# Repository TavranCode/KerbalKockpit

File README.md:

# KerbalKockpit
A custom control panel for Kerbal Space Program. Heavily cribbed from PeteWasEre

This repository is a place for me to keep and share my code, designs and data for my custom KSP Control Panel.

The contents are:

1. Arduino Code - The modules that run on the Arduino Duemilanove
2. Documentation - Doesn't exist yet!
3. Enclosure Design - The printed graphics used on the panels. Designed to print to a Glowforge
4. PCB design - what it says on the tin.
5. Python Code - The python module that runs at the PC end of the link

If it helps you then please use it. Better yet, consult the original.

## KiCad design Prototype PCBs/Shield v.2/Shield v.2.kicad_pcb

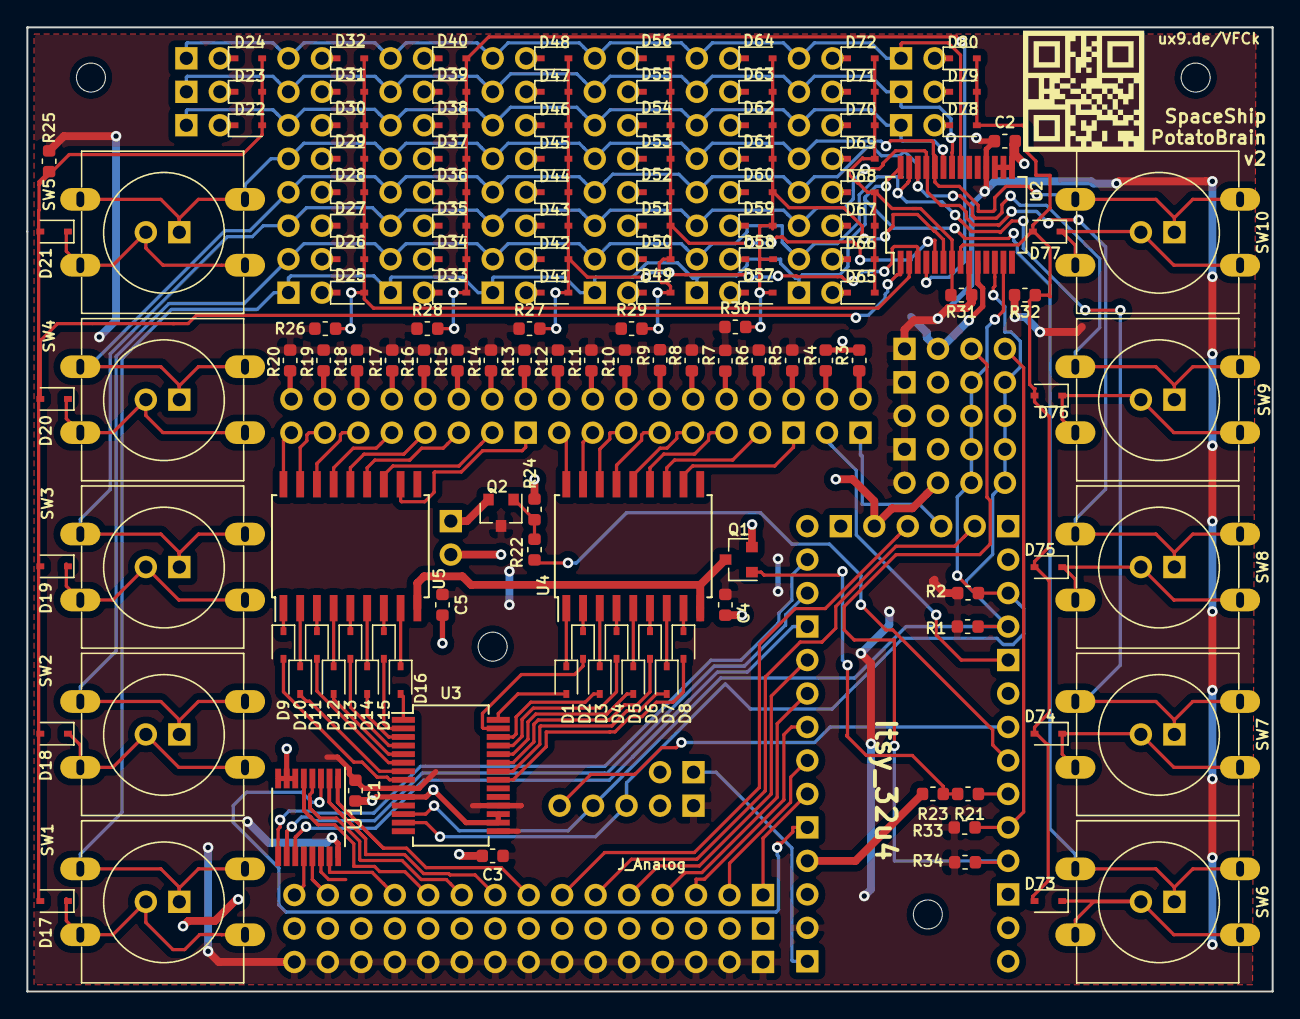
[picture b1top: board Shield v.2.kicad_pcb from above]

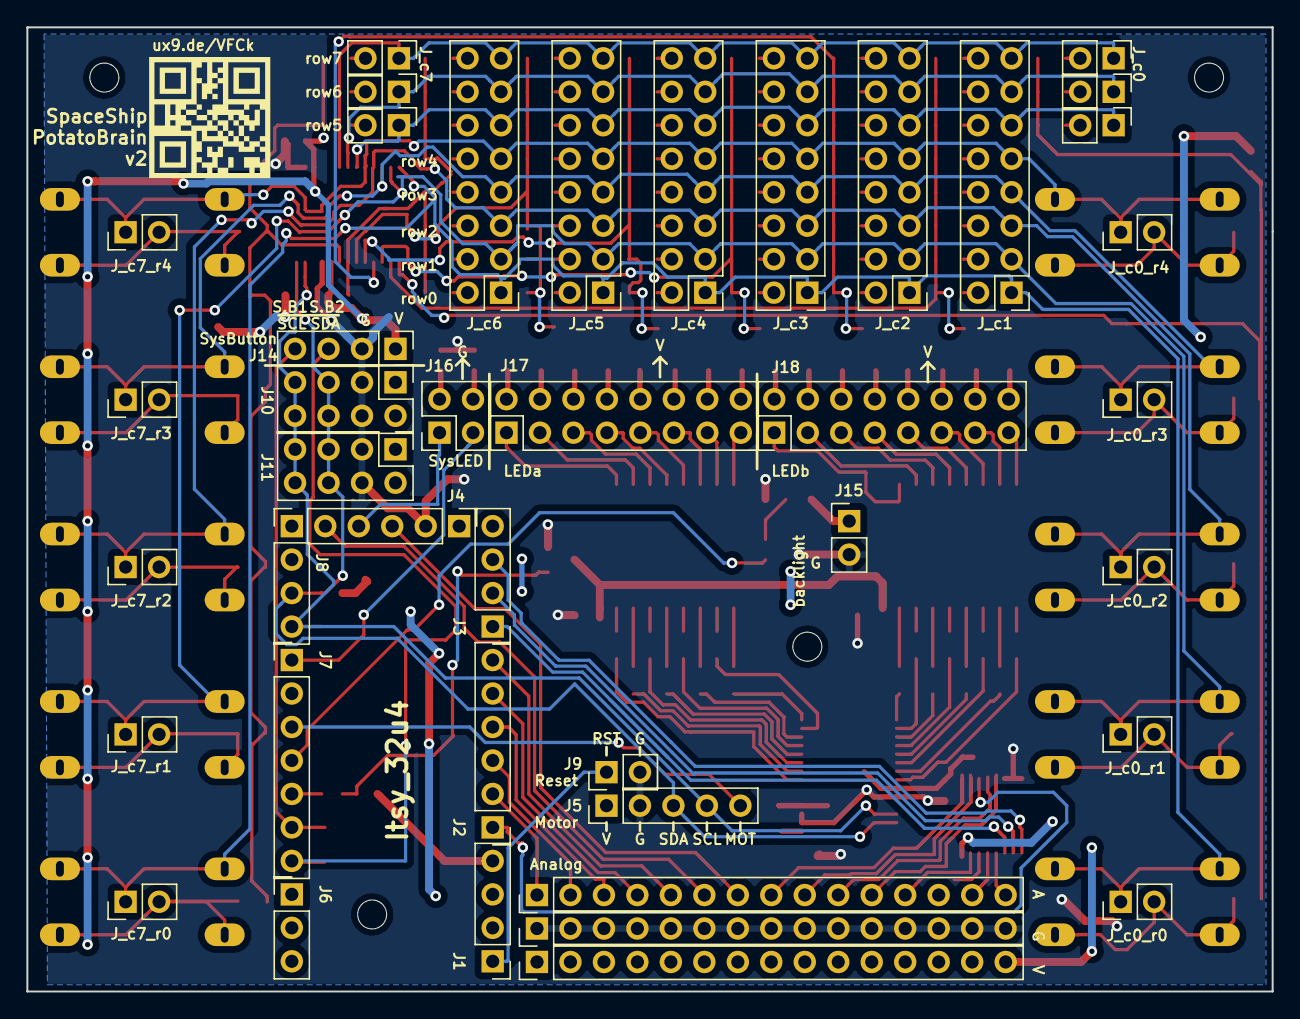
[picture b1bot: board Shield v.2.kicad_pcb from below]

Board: 2 copper layers, 94.5 x 73.2 mm, 183 parts (42 on the bottom side), 181 nets.

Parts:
A: Conn_01x15; PinHeader_1x15_P2.54mm_Vertical
C1, C2, C3, C4, C5: C; C_0603_1608Metric
D1, D2, D3, D4, D5, D6, D7, D8, D9, D10, D11, D12, D13, D14, D15, D16: D; D_SOD-323
D17, D18, D19, D20, D21, D22, D23, D24, D25, D26, D27, D28, D29, D30, D31, D32, D33, D34, D35, D36, D37, D38, D39, D40, D41, D42, D43, D44, D45, D46, D47, D48, D49, D50, D51, D52, D53, D54, D55, D56, D57, D58, D59, D60, D61, D62, D63, D64, D65, D66, D67, D68, D69, D70, D71, D72, D73, D74, D75, D76, D77, D78, D79, D80: 1N4148; D_SOD-323
G: Conn_01x15; PinHeader_1x15_P2.54mm_Vertical
J1, J3, J8: Conn_01x04; PinHeader_1x04_P2.54mm_Vertical
J2: Conn_01x06; PinHeader_1x06_P2.54mm_Vertical
J4: Conn_01x05; PinHeader_1x05_P2.54mm_Vertical
J5: Motor; PinHeader_1x05_P2.54mm_Vertical
J6: Conn_01x03; PinHeader_1x03_P2.54mm_Vertical
J7: Conn_01x07; PinHeader_1x07_P2.54mm_Vertical
J9: Conn_Reset; PinHeader_1x02_P2.54mm_Vertical
J10: i2cA; PinHeader_2x04_P2.54mm_Vertical
J11: i2cB; PinHeader_2x04_P2.54mm_Vertical
J14: Conn_SysBut; PinHeader_1x04_P2.54mm_Vertical
J15: Conn_bLight; PinHeader_1x02_P2.54mm_Vertical
J16: Conn_SysLED; PinHeader_2x02_P2.54mm_Vertical
J17: LEDs_A; PinHeader_2x08_P2.54mm_Vertical
J18: LEDs_B; PinHeader_2x08_P2.54mm_Vertical
J19F2, J19G1, J26F1, J26G1: Jumper_NO_Small; PinHeader_1x02_P2.54mm_Vertical
J_c0, J_c0_r0, J_c0_r1, J_c0_r2, J_c0_r3, J_c0_r4, J_c7, J_c7_r0, J_c7_r1, J_c7_r2, J_c7_r3, J_c7_r4: Jumper_NO_Small; PinHeader_1x02_P2.54mm_Vertical
J_c1, J_c2, J_c3, J_c4, J_c5, J_c6: JumpSwitch; PinHeader_2x08_P2.54mm_Vertical
Mount1, Mount2, Mount3, Mount4: MountingHole_2.2mm_M2
Q1, Q2: Q_NMOS_DIM; SOT-23
QR*****: ux9.de/VFCk; ux9.de_VFCk
QR*****#2: ux9.de/VFCk; ux9.de_VFCk
R1, R2, R23, R24, R25, R26, R27, R28, R29, R30, R31, R32, R33, R34: R4.7k; R_0603_1608Metric
R3, R4, R5, R6, R7, R8, R9, R10, R11, R12, R13, R14, R15, R16, R17, R18, R19, R20: R; R_0603_1608Metric
R21, R22: R1k; R_0603_1608Metric
SW1, SW2, SW3, SW4, SW5, SW6, SW7, SW8, SW9, SW10: SW_Push; SW_PUSH-12mm_widepinholes
U1: 74HC4051; TSSOP-16_4.4x5mm_P0.65mm
U2: MCP23017_0x20_in; SSOP-28_5.3x10.2mm_P0.65mm
U3: MCP23017_0x21_out; SSOP-28_5.3x10.2mm_P0.65mm
U4, U5: ULN2803A; SOIC-18W_7.5x11.6mm_P1.27mm
V: Conn_01x15; PinHeader_1x15_P2.54mm_Vertical

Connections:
+5V: C1.1, C2.1, C3.1, C4.1, C5.1, J1.2, J5.1, J10.1, J10.2, J11.1, J11.2, J14.1, Q2.3, R1.1, R2.1, R5.1, R6.1, R7.1, R8.1, R9.1, R10.1, R11.1, R12.1, R13.1, R14.1, R15.1, R16.1, R17.1, R18.1, R19.1, R20.1, R25.1, R26.1, R27.1, R28.1, R29.1, R30.1, R31.1, R32.1, R33.1, R34.1, U1.16, U2.9, U2.18, U3.9, U3.15, U3.18, V.1, V.2, V.3, V.4, V.5, V.6, V.7, V.8, V.9, V.10, V.11, V.12, V.13, V.14, V.15
/5*: J7.1, J16.3
/9*: J5.5, J7.3
/10*: J7.4, R22.2
/11*: J7.5, R21.2
/12: J7.6, J14.4, R33.2
/13: J7.7, J14.3, R34.2
/14: J3.3, U1.9
/15: J3.1, U1.11
/16: J3.2, U1.10
/A0: J2.1, U1.3
/A1: A.1, J2.2
/A2: A.2, J2.3
/A3: A.3, J2.4
/A4: A.4, J2.5
/A5: A.5, J2.6
/A6: A.6, J4.5
/A7: J4.4, J16.1
/A8: A.7, J4.3
/DIM: Q1.3, U4.9, U5.9
/Input Matrix/input_c0: D17.2, D18.2, D19.2, D20.2, D21.2, D22.2, D23.2, D24.2, R25.2, U2.1
/Input Matrix/input_c1: D25.2, D26.2, D27.2, D28.2, D29.2, D30.2, D31.2, D32.2, R26.2, U2.2
/Input Matrix/input_c2: D33.2, D34.2, D35.2, D36.2, D37.2, D38.2, D39.2, D40.2, R28.2, U2.4
/Input Matrix/input_c3: D41.2, D42.2, D43.2, D44.2, D45.2, D46.2, D47.2, D48.2, R27.2, U2.3
/Input Matrix/input_c4: D49.2, D50.2, D51.2, D52.2, D53.2, D54.2, D55.2, D56.2, R29.2, U2.5
/Input Matrix/input_c5: D57.2, D58.2, D59.2, D60.2, D61.2, D62.2, D63.2, D64.2, R30.2, U2.6
/Input Matrix/input_c6: D65.2, D66.2, D67.2, D68.2, D69.2, D70.2, D71.2, D72.2, R31.2, U2.7
/Input Matrix/input_c7: D73.2, D74.2, D75.2, D76.2, D77.2, D78.2, D79.2, D80.2, R32.2, U2.8
/Input Matrix/input_r0: J_c0_r0.1, J_c1.1, J_c2.1, J_c3.1, J_c4.1, J_c5.1, J_c6.1, J_c7_r0.1, SW1.1, SW6.1, U2.28
/Input Matrix/input_r1: J_c0_r1.1, J_c1.3, J_c2.3, J_c3.3, J_c4.3, J_c5.3, J_c6.3, J_c7_r1.1, SW2.1, SW7.1, U2.27
/Input Matrix/input_r2: J_c0_r2.1, J_c1.5, J_c2.5, J_c3.5, J_c4.5, J_c5.5, J_c6.5, J_c7_r2.1, SW3.1, SW8.1, U2.25
/Input Matrix/input_r3: J_c0_r3.1, J_c1.7, J_c2.7, J_c3.7, J_c4.7, J_c5.7, J_c6.7, J_c7_r3.1, SW4.1, SW9.1, U2.26
/Input Matrix/input_r4: J_c0_r4.1, J_c1.9, J_c2.9, J_c3.9, J_c4.9, J_c5.9, J_c6.9, J_c7_r4.1, SW5.1, SW10.1, U2.24
/Input Matrix/input_r5: J19F2.1, J26F1.1, J_c1.11, J_c2.11, J_c3.11, J_c4.11, J_c5.11, J_c6.11, U2.23
/Input Matrix/input_r6: J19G1.1, J26G1.1, J_c1.13, J_c2.13, J_c3.13, J_c4.13, J_c5.13, J_c6.13, U2.22
/Input Matrix/input_r7: J_c0.1, J_c1.15, J_c2.15, J_c3.15, J_c4.15, J_c5.15, J_c6.15, J_c7.1, U2.21
/O.A0: D9.1, U5.1
/O.A1: D10.1, U5.2
/O.A2: D11.1, U5.3
/O.A3: D12.1, U5.4
/O.A4: D13.1, U5.5
/O.A5: D14.1, U5.6
/O.A6: D15.1, U5.7
/O.A7: D16.1, U5.8
/O.B0: D1.1, U4.1
/O.B1: D2.1, U4.2
/O.B2: D3.1, U4.3
/O.B3: D4.1, U4.4
/O.B4: D5.1, U4.5
/O.B5: D6.1, U4.6
/O.B6: D7.1, U4.7
/O.B7: D8.1, U4.8
/RST: J1.1, J9.1
/SCL: J5.4, J8.4, J10.7, J10.8, J11.7, J11.8, R1.2, U2.12, U3.12
/SDA: J5.3, J8.3, J10.5, J10.6, J11.5, J11.6, R2.2, U2.13, U3.13
/uA0: A.14, U1.13
/uA1: A.13, U1.14
/uA2: A.12, U1.15
/uA3: A.15, U1.12
/uA4: A.8, U1.1
/uA5: A.11, U1.5
/uA6: A.9, U1.2
/uA7: A.10, U1.4
GND: C1.2, C2.2, C3.2, C4.2, C5.2, G.1, G.2, G.3, G.4, G.5, G.6, G.7, G.8, G.9, G.10, G.11, G.12, G.13, G.14, G.15, J1.4, J4.2, J5.2, J9.2, J10.3, J10.4, J11.3, J11.4, J14.2, J15.2, Q1.2, R3.1, R4.1, R23.1, R24.1, U1.6, U1.7, U1.8, U2.10, U2.15, U2.16, U2.17, U3.10, U3.16, U3.17
unnamed: D1.2, U3.28
unnamed: D2.2, U3.27
unnamed: D3.2, U3.26
unnamed: D4.2, U3.25
unnamed: D5.2, U3.24
unnamed: D6.2, U3.23
unnamed: D7.2, U3.22
unnamed: D8.2, U3.21
unnamed: D9.2, U3.8
unnamed: D10.2, U3.7
unnamed: D11.2, U3.6
unnamed: D12.2, U3.5
unnamed: D13.2, U3.4
unnamed: D14.2, U3.3
unnamed: D15.2, U3.2
unnamed: D16.2, U3.1
unnamed: D17.1, J_c0_r0.2, SW1.2
unnamed: D18.1, J_c0_r1.2, SW2.2
unnamed: D19.1, J_c0_r2.2, SW3.2
unnamed: D20.1, J_c0_r3.2, SW4.2
unnamed: D21.1, J_c0_r4.2, SW5.2
unnamed: D22.1, J19F2.2
unnamed: D23.1, J19G1.2
unnamed: D24.1, J_c0.2
unnamed: D25.1, J_c1.2
unnamed: D26.1, J_c1.4
unnamed: D27.1, J_c1.6
unnamed: D28.1, J_c1.8
unnamed: D29.1, J_c1.10
unnamed: D30.1, J_c1.12
unnamed: D31.1, J_c1.14
unnamed: D32.1, J_c1.16
unnamed: D33.1, J_c2.2
unnamed: D34.1, J_c2.4
unnamed: D35.1, J_c2.6
unnamed: D36.1, J_c2.8
unnamed: D37.1, J_c2.10
unnamed: D38.1, J_c2.12
unnamed: D39.1, J_c2.14
unnamed: D40.1, J_c2.16
unnamed: D41.1, J_c3.2
unnamed: D42.1, J_c3.4
unnamed: D43.1, J_c3.6
unnamed: D44.1, J_c3.8
unnamed: D45.1, J_c3.10
unnamed: D46.1, J_c3.12
unnamed: D47.1, J_c3.14
unnamed: D48.1, J_c3.16
unnamed: D49.1, J_c4.2
unnamed: D50.1, J_c4.4
unnamed: D51.1, J_c4.6
unnamed: D52.1, J_c4.8
unnamed: D53.1, J_c4.10
unnamed: D54.1, J_c4.12
unnamed: D55.1, J_c4.14
unnamed: D56.1, J_c4.16
unnamed: D57.1, J_c5.2
unnamed: D58.1, J_c5.4
unnamed: D59.1, J_c5.6
unnamed: D60.1, J_c5.8
unnamed: D61.1, J_c5.10
unnamed: D62.1, J_c5.12
unnamed: D63.1, J_c5.14
unnamed: D64.1, J_c5.16
unnamed: D65.1, J_c6.2
unnamed: D66.1, J_c6.4
unnamed: D67.1, J_c6.6
unnamed: D68.1, J_c6.8
unnamed: D69.1, J_c6.10
unnamed: D70.1, J_c6.12
unnamed: D71.1, J_c6.14
unnamed: D72.1, J_c6.16
unnamed: D73.1, J_c7_r0.2, SW6.2
unnamed: D74.1, J_c7_r1.2, SW7.2
unnamed: D75.1, J_c7_r2.2, SW8.2
unnamed: D76.1, J_c7_r3.2, SW9.2
unnamed: D77.1, J_c7_r4.2, SW10.2
unnamed: D78.1, J26F1.2
unnamed: D79.1, J26G1.2
unnamed: D80.1, J_c7.2
unnamed: J15.1, Q2.2
unnamed: J16.2, R3.2
unnamed: J16.4, R4.2
unnamed: J17.1, U4.11
unnamed: J17.2, R5.2
unnamed: J17.3, U4.12
unnamed: J17.4, R6.2
unnamed: J17.5, U4.13
unnamed: J17.6, R7.2
unnamed: J17.7, U4.14
unnamed: J17.8, R8.2
unnamed: J17.9, U4.15
unnamed: J17.10, R9.2
unnamed: J17.11, U4.16
unnamed: J17.12, R10.2
unnamed: J17.13, U4.17
unnamed: J17.14, R11.2
unnamed: J17.15, U4.18
unnamed: J17.16, R12.2
unnamed: J18.1, U5.11
unnamed: J18.2, R13.2
unnamed: J18.3, U5.12
unnamed: J18.4, R14.2
unnamed: J18.5, U5.13
unnamed: J18.6, R15.2
unnamed: J18.7, U5.14
unnamed: J18.8, R16.2
unnamed: J18.9, U5.15
unnamed: J18.10, R17.2
unnamed: J18.11, U5.16
unnamed: J18.12, R18.2
unnamed: J18.13, U5.17
unnamed: J18.14, R19.2
unnamed: J18.15, U5.18
unnamed: J18.16, R20.2
unnamed: Q1.1, R21.1, R23.2
unnamed: Q2.1, R22.1, R24.2

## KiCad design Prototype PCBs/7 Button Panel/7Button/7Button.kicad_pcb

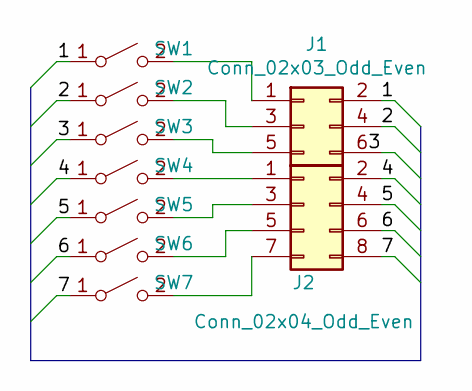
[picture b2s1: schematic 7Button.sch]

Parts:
J1: Conn_02x03_Odd_Even; PinHeader_2x03_P2.54mm_Vertical
J2: Conn_02x04_Odd_Even; PinHeader_2x04_P2.54mm_Vertical
SW1, SW2, SW3, SW4, SW5, SW6, SW7: SW_SPST; SW_PUSH-12mm_widepinholes

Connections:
/1: J1.2, SW1.1 (A)
/2: J1.4, SW2.1 (A)
/3: J1.6, SW3.1 (A)
/4: J2.2, SW4.1 (A)
/5: J2.4, SW5.1 (A)
/6: J2.6, SW6.1 (A)
/7: J2.8, SW7.1 (A)
unnamed: J1.1, SW1.2 (B)
unnamed: J1.3, SW2.2 (B)
unnamed: J1.5, SW3.2 (B)
unnamed: J2.1, SW4.2 (B)
unnamed: J2.3, SW5.2 (B)
unnamed: J2.5, SW6.2 (B)
unnamed: J2.7, SW7.2 (B)

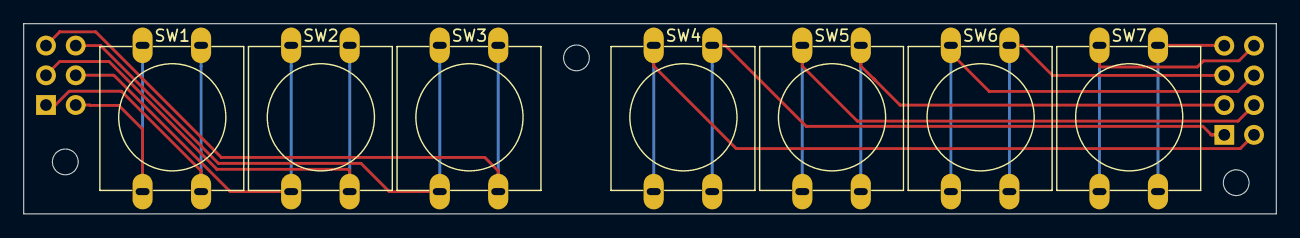
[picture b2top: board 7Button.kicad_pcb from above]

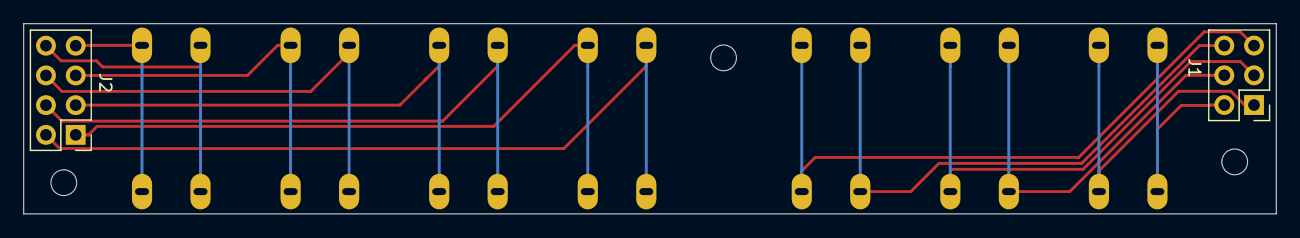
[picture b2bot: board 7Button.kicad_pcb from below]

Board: 2 copper layers, 107.1 x 16.3 mm, 9 parts (2 on the bottom side), 14 nets.

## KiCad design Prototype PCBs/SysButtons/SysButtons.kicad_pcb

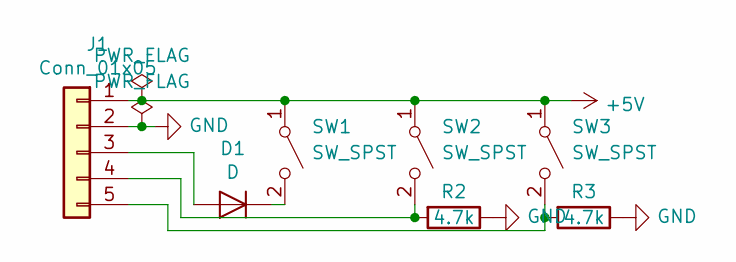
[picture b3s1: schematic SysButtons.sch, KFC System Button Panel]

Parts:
D1: D; D_DO-35_SOD27_P7.62mm_Horizontal
J1: Conn_01x05; PinHeader_1x05_P2.54mm_Vertical
R2, R3: 4.7k; R_Axial_DIN0207_L6.3mm_D2.5mm_P7.62mm_Horizontal
SW1, SW2, SW3: SW_SPST; SW_PUSH-12mm_widepinholes

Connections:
+5V: J1.1, SW1.1 (A), SW2.1 (A), SW3.1 (A)
GND: J1.2, R2.1, R3.1
unnamed: D1.1 (K), SW1.2 (B)
unnamed: D1.2 (A), J1.3
unnamed: J1.4, R2.2, SW2.2 (B)
unnamed: J1.5, R3.2, SW3.2 (B)

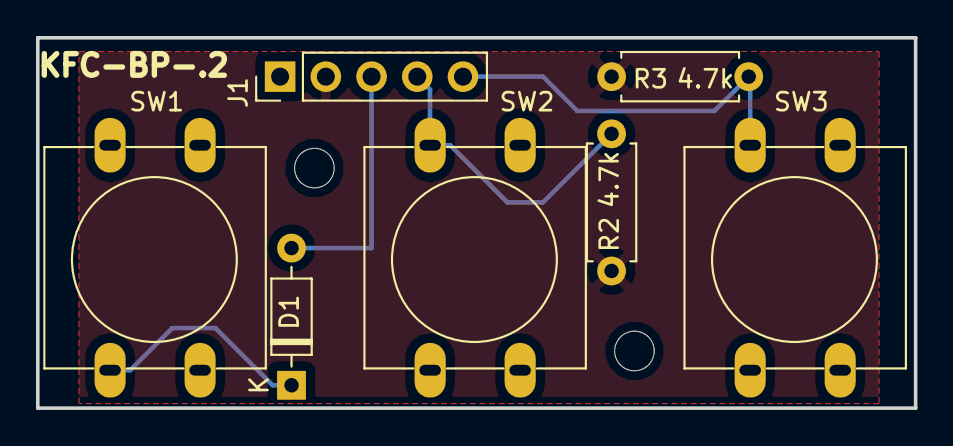
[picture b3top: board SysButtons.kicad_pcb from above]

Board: 2 copper layers, 48.8 x 20.6 mm, 7 parts (0 on the bottom side), 6 nets.

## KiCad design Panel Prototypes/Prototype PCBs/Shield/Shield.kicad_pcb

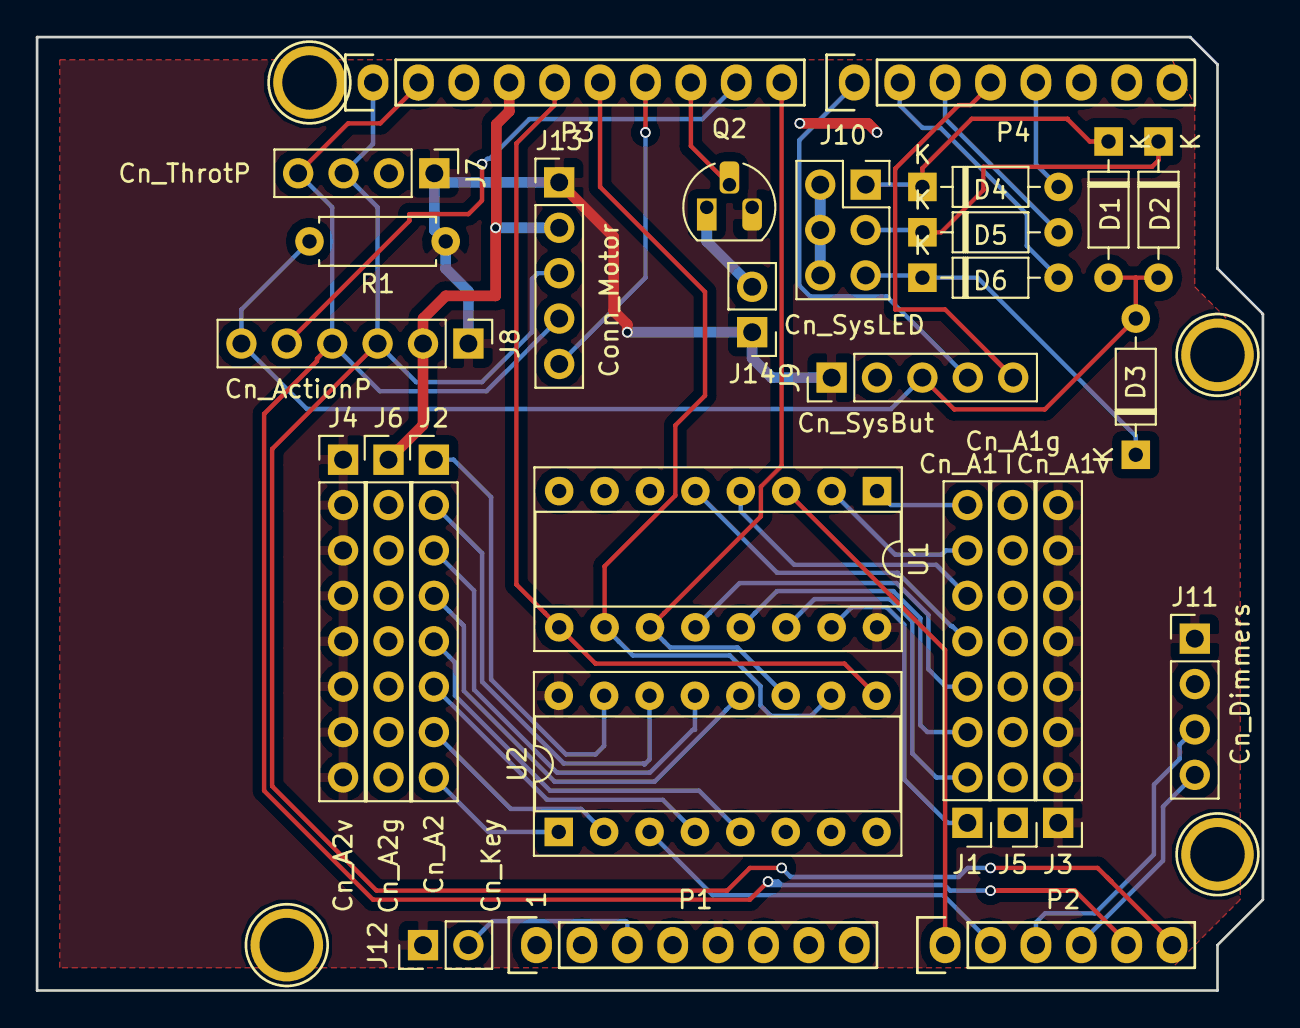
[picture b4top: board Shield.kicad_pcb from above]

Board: 2 copper layers, 68.6 x 53.3 mm, 32 parts (0 on the bottom side), 41 nets.

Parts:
D1, D2, D3, D4, D5, D6: D; D_DO-35_SOD27_P7.62mm_Horizontal
J1: Cn_A1; PinHeader_1x08_P2.54mm_Vertical
J2: Cn_A2; PinHeader_1x08_P2.54mm_Vertical
J3: Cn_A1v; PinHeader_1x08_P2.54mm_Vertical
J4: Cn_A2v; PinHeader_1x08_P2.54mm_Vertical
J5: Cn_A1g; PinHeader_1x08_P2.54mm_Vertical
J6: Cn_A2g; PinHeader_1x08_P2.54mm_Vertical
J7: Cn_ThrotP; PinHeader_1x04_P2.54mm_Vertical
J8: Cn_ActionP; PinHeader_1x06_P2.54mm_Vertical
J9: Cn_SysBut; PinHeader_1x05_P2.54mm_Vertical
J10: Cn_SysLED; PinSocket_2x03_P2.54mm_Vertical
J11: Cn_Dimmers; PinHeader_1x04_P2.54mm_Vertical
J12: Cn_Key; PinHeader_1x02_P2.54mm_Vertical
J13: Conn_Motor; PinHeader_1x05_P2.54mm_Vertical
J14: Cn_Back; PinHeader_1x02_P2.54mm_Vertical
P1: Power; Socket_Strip_Arduino_1x08
P2: Analog; Socket_Strip_Arduino_1x06
P3: Digital; Socket_Strip_Arduino_1x10
P4: Digital; Socket_Strip_Arduino_1x08
P5, P6, P7, P8: CONN_01X01; Arduino_1pin
Q2: 2N2219; TO-92_HandSolder
R1: 10k; R_Axial_DIN0207_L6.3mm_D2.5mm_P7.62mm_Horizontal
U1, U2: 74HC4051; DIP-16_W7.62mm_Socket

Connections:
+5V: J3.1, J3.2, J3.3, J3.4, J3.5, J3.6, J3.7, J3.8, J4.1, J4.2, J4.3, J4.4, J4.5, J4.6, J4.7, J4.8, J7.1, J8.1, J9.1, J11.1, J12.1, J13.1, J14.1, P1.5, Q2.3, R1.1, U1.16, U2.16
/3(**): D4.2, P4.5
/4: J9.5, P4.4
/5(**): D5.2, P4.3
/6(**): D6.2, P4.2
/7: J9.4, P4.1
/8: P3.10, U1.11, U2.11
/9(**): J8.5, P3.9
/10(**/SS): P3.8, Q2.2
/11(**/MOSI): J13.5, P3.7
/12(MISO): P3.6, U1.10, U2.10
/13(SCK): P3.5, U1.9, U2.9
/A0: P2.1, U1.3
/A1: P2.2, U2.3
/A2: J11.3, P2.3
/A3: J11.4, P2.4
/A4(SDA): J7.4, J8.4, J13.4, P2.5, P3.2
/A5(SCL): J7.3, J8.3, J13.3, P2.6, P3.1
/Au1: J2.4, U2.12
/Au2: J2.8, U2.1
/Au3: J2.5, U2.5
/Au4: J2.7, U2.2
/Au5: J2.6, U2.4
/Crx: J1.8, U1.1
/Cry: J1.5, U1.5
/Ctx: J1.7, U1.2
/Cty: J1.6, U1.4
/Ltest: D1.2, D2.2, D3.2, J8.6, J9.3, R1.2
/R_x: J2.3, U2.13
/R_y: J2.2, U2.14
/R_z: J2.1, U2.15
/Reset: J12.2, P1.3
/T_x: J1.3, U1.13
/T_y: J1.2, U1.14
/T_z: J1.1, U1.15
/Thr: J1.4, U1.12
GND: J5.1, J5.2, J5.3, J5.4, J5.5, J5.6, J5.7, J5.8, J6.1, J6.2, J6.3, J6.4, J6.5, J6.6, J6.7, J6.8, J7.2, J8.2, J9.2, J10.2, J10.4, J10.6, J11.2, J13.2, P1.6, P1.7, P3.4, U1.6, U1.7, U1.8, U2.6, U2.7, U2.8
unnamed: D1.1, D4.1, J10.1
unnamed: D2.1, D5.1, J10.3
unnamed: D3.1, D6.1, J10.5
unnamed: J14.2, Q2.1

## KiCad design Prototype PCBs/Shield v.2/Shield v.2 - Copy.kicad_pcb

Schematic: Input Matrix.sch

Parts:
D1, D2, D3, D4, D5, D6, D7, D8, D9, D10, D11, D12, D13, D14, D15, D16, D17, D18, D19, D20, D21, D22, D23, D24, D25, D26, D27, D28, D29, D30, D31, D32, D33, D34, D35, D36, D37, D38, D39, D40, D41, D42, D43, D44, D45, D46, D47, D48, D49, D50, D51, D52, D53, D54, D55, D56, D57, D58, D59, D60, D61, D62, D63, D64: 1N4148; D_SOD-323
J1, J2, J3, J4, J5, J6, J7, J8: JumpSwitch; PinHeader_2x08_P2.54mm_Vertical
SW1, SW2, SW3, SW4, SW5, SW6, SW7, SW8, SW9, SW10: SW_Push; SW_SPST_B3S-1000

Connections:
/Input Matrix/input_c0: D1.2 (A), D2.2 (A), D6.2 (A), D7.2 (A), D8.2 (A); also elsewhere on the board
/Input Matrix/input_c1: D9.2 (A), D10.2 (A), D11.2 (A), D12.2 (A), D13.2 (A), D14.2 (A), D15.2 (A), D16.2 (A); also elsewhere on the board
/Input Matrix/input_c2: D17.2 (A), D18.2 (A), D19.2 (A), D20.2 (A), D21.2 (A), D22.2 (A), D23.2 (A), D24.2 (A); also elsewhere on the board
/Input Matrix/input_c3: D25.2 (A), D26.2 (A), D27.2 (A), D28.2 (A), D29.2 (A), D30.2 (A), D31.2 (A), D32.2 (A); also elsewhere on the board
/Input Matrix/input_c4: D33.2 (A), D34.2 (A), D35.2 (A), D36.2 (A), D37.2 (A), D38.2 (A), D39.2 (A), D40.2 (A); also elsewhere on the board
/Input Matrix/input_c5: D41.2 (A), D42.2 (A), D43.2 (A), D44.2 (A), D45.2 (A), D46.2 (A), D47.2 (A), D48.2 (A); also elsewhere on the board
/Input Matrix/input_c6: D49.2 (A), D50.2 (A), D51.2 (A), D52.2 (A), D53.2 (A), D54.2 (A), D55.2 (A), D56.2 (A); also elsewhere on the board
/Input Matrix/input_c7: D57.2 (A), D58.2 (A), D59.2 (A), D60.2 (A), D61.2 (A), D62.2 (A), D63.2 (A), D64.2 (A); also elsewhere on the board
/Input Matrix/input_r0: J1.1, J2.1, J3.1, J4.1, J5.1, J6.1, J7.1, J8.1, SW1.1, SW6.1; also elsewhere on the board
/Input Matrix/input_r1: J1.3, J2.3, J3.3, J4.3, J5.3, J6.3, J7.3, J8.3, SW2.1, SW7.1; also elsewhere on the board
/Input Matrix/input_r2: J2.5, J3.5, J4.5, J5.5, J6.5, J7.5, J8.5, SW3.1, SW8.1; also elsewhere on the board
/Input Matrix/input_r3: J2.7, J3.7, J4.7, J5.7, J6.7, J7.7, J8.7, SW4.1, SW9.1; also elsewhere on the board
/Input Matrix/input_r4: J2.9, J3.9, J4.9, J5.9, J6.9, J7.9, J8.9, SW5.1, SW10.1; also elsewhere on the board
/Input Matrix/input_r5: J1.11, J2.11, J3.11, J4.11, J5.11, J6.11, J7.11, J8.11; also elsewhere on the board
/Input Matrix/input_r6: J1.13, J2.13, J3.13, J4.13, J5.13, J6.13, J7.13, J8.13; also elsewhere on the board
/Input Matrix/input_r7: J1.15, J2.15, J3.15, J4.15, J5.15, J6.15, J7.15, J8.15; also elsewhere on the board
unnamed: D1.1 (K), J1.2, SW1.2
unnamed: D2.1 (K), J1.4, SW2.2
unnamed: D3.1 (K), J1.6, SW3.2
unnamed: D4.1 (K), J1.8, SW4.2
unnamed: D5.1 (K), J1.10, SW5.2
unnamed: D6.1 (K), J1.12
unnamed: D7.1 (K), J1.14
unnamed: D8.1 (K), J1.16
unnamed: D9.1 (K), J2.2
unnamed: D10.1 (K), J2.4
unnamed: D11.1 (K), J2.6
unnamed: D12.1 (K), J2.8
unnamed: D13.1 (K), J2.10
unnamed: D14.1 (K), J2.12
unnamed: D15.1 (K), J2.14
unnamed: D16.1 (K), J2.16
unnamed: D17.1 (K), J3.2
unnamed: D18.1 (K), J3.4
unnamed: D19.1 (K), J3.6
unnamed: D20.1 (K), J3.8
unnamed: D21.1 (K), J3.10
unnamed: D22.1 (K), J3.12
unnamed: D23.1 (K), J3.14
unnamed: D24.1 (K), J3.16
unnamed: D25.1 (K), J4.2
unnamed: D26.1 (K), J4.4
unnamed: D27.1 (K), J4.6
unnamed: D28.1 (K), J4.8
unnamed: D29.1 (K), J4.10
unnamed: D30.1 (K), J4.12
unnamed: D31.1 (K), J4.14
unnamed: D32.1 (K), J4.16
unnamed: D33.1 (K), J5.2
unnamed: D34.1 (K), J5.4
unnamed: D35.1 (K), J5.6
unnamed: D36.1 (K), J5.8
unnamed: D37.1 (K), J5.10
unnamed: D38.1 (K), J5.12
unnamed: D39.1 (K), J5.14
unnamed: D40.1 (K), J5.16
unnamed: D41.1 (K), J6.2
unnamed: D42.1 (K), J6.4
unnamed: D43.1 (K), J6.6
unnamed: D44.1 (K), J6.8
unnamed: D45.1 (K), J6.10
unnamed: D46.1 (K), J6.12
unnamed: D47.1 (K), J6.14
unnamed: D48.1 (K), J6.16
unnamed: D49.1 (K), J7.2
unnamed: D50.1 (K), J7.4
unnamed: D51.1 (K), J7.6
unnamed: D52.1 (K), J7.8
unnamed: D53.1 (K), J7.10
unnamed: D54.1 (K), J7.12
unnamed: D55.1 (K), J7.14
unnamed: D56.1 (K), J7.16
unnamed: D57.1 (K), J8.2, SW6.2
unnamed: D58.1 (K), J8.4, SW7.2
unnamed: D59.1 (K), J8.6, SW8.2
unnamed: D60.1 (K), J8.8, SW9.2
unnamed: D61.1 (K), J8.10, SW10.2
unnamed: D62.1 (K), J8.12
unnamed: D63.1 (K), J8.14
unnamed: D64.1 (K), J8.16

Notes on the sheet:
Shield V2 8x8

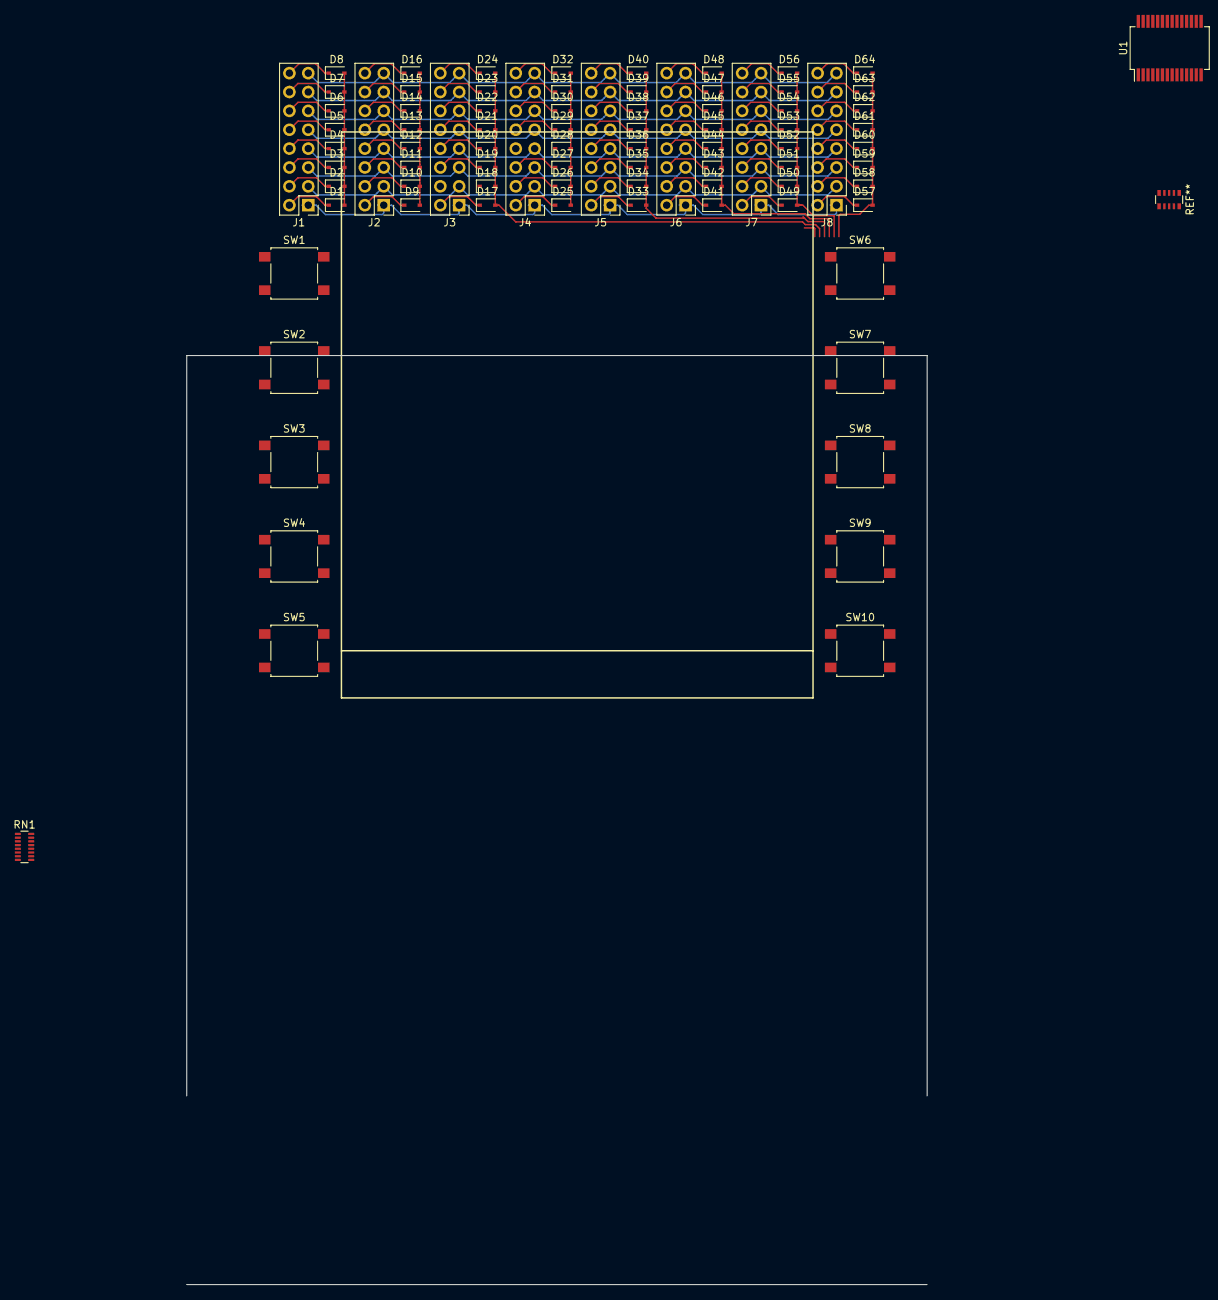
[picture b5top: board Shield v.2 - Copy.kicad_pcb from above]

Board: 2 copper layers, 84 parts (0 on the bottom side), 80 nets.

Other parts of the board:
RN1: R_Network08_US; R_Array_Convex_8x0602
U1: MCP23017_SS; SSOP-28_5.3x10.2mm_P0.65mm

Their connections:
/Input Matrix/input_c0: U1.28; also elsewhere on the board
/Input Matrix/input_c1: U1.27; also elsewhere on the board
/Input Matrix/input_c2: U1.25; also elsewhere on the board
/Input Matrix/input_c3: U1.26; also elsewhere on the board
/Input Matrix/input_c4: U1.24; also elsewhere on the board
/Input Matrix/input_c5: U1.23; also elsewhere on the board
/Input Matrix/input_c6: U1.22; also elsewhere on the board
/Input Matrix/input_c7: U1.21; also elsewhere on the board
/Input Matrix/input_r0: RN1.2, U1.1; also elsewhere on the board
/Input Matrix/input_r1: RN1.3, U1.2; also elsewhere on the board
/Input Matrix/input_r2: RN1.5, U1.4; also elsewhere on the board
/Input Matrix/input_r3: RN1.4, U1.3; also elsewhere on the board
/Input Matrix/input_r4: RN1.6, U1.5; also elsewhere on the board
/Input Matrix/input_r5: RN1.7, U1.6; also elsewhere on the board
/Input Matrix/input_r6: RN1.8, U1.7; also elsewhere on the board
/Input Matrix/input_r7: RN1.9, U1.8; also elsewhere on the board

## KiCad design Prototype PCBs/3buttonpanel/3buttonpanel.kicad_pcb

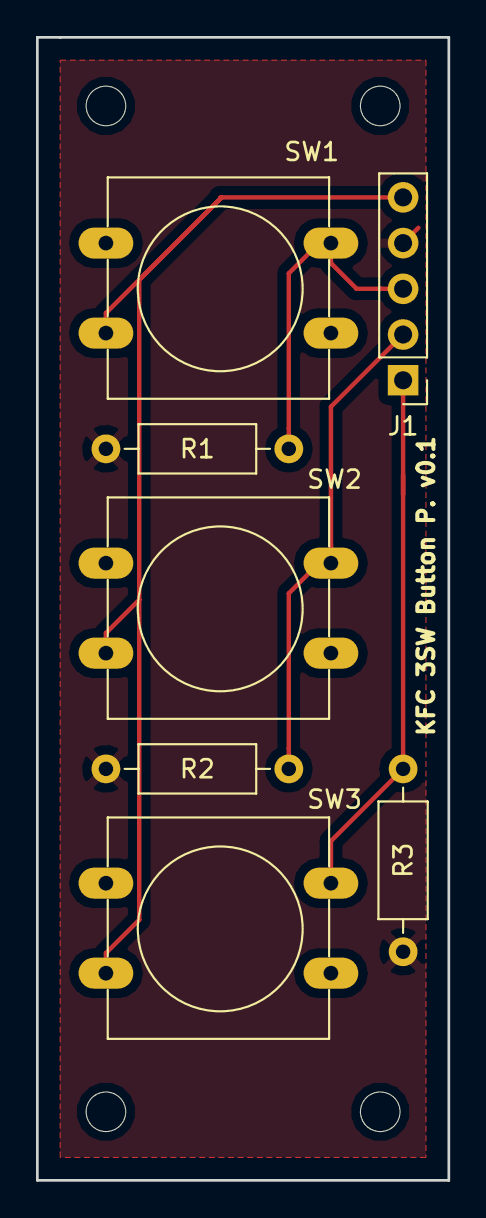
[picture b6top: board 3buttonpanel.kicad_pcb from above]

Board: 2 copper layers, 22.9 x 63.5 mm, 7 parts (0 on the bottom side), 5 nets.

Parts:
J1: Conn_01x05; PinHeader_1x05_P2.54mm_Vertical
R1, R2, R3: R_US; R_Axial_DIN0207_L6.3mm_D2.5mm_P10.16mm_Horizontal
SW1, SW2, SW3: SW_SPST; SW_PUSH-12mm

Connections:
GND: J1.4, R1.1, R2.1, R3.1
unnamed: J1.1, R3.2, SW3.1
unnamed: J1.2, R2.2, SW2.1
unnamed: J1.3, R1.2, SW1.1
VCC: J1.5, SW1.2, SW2.2, SW3.2

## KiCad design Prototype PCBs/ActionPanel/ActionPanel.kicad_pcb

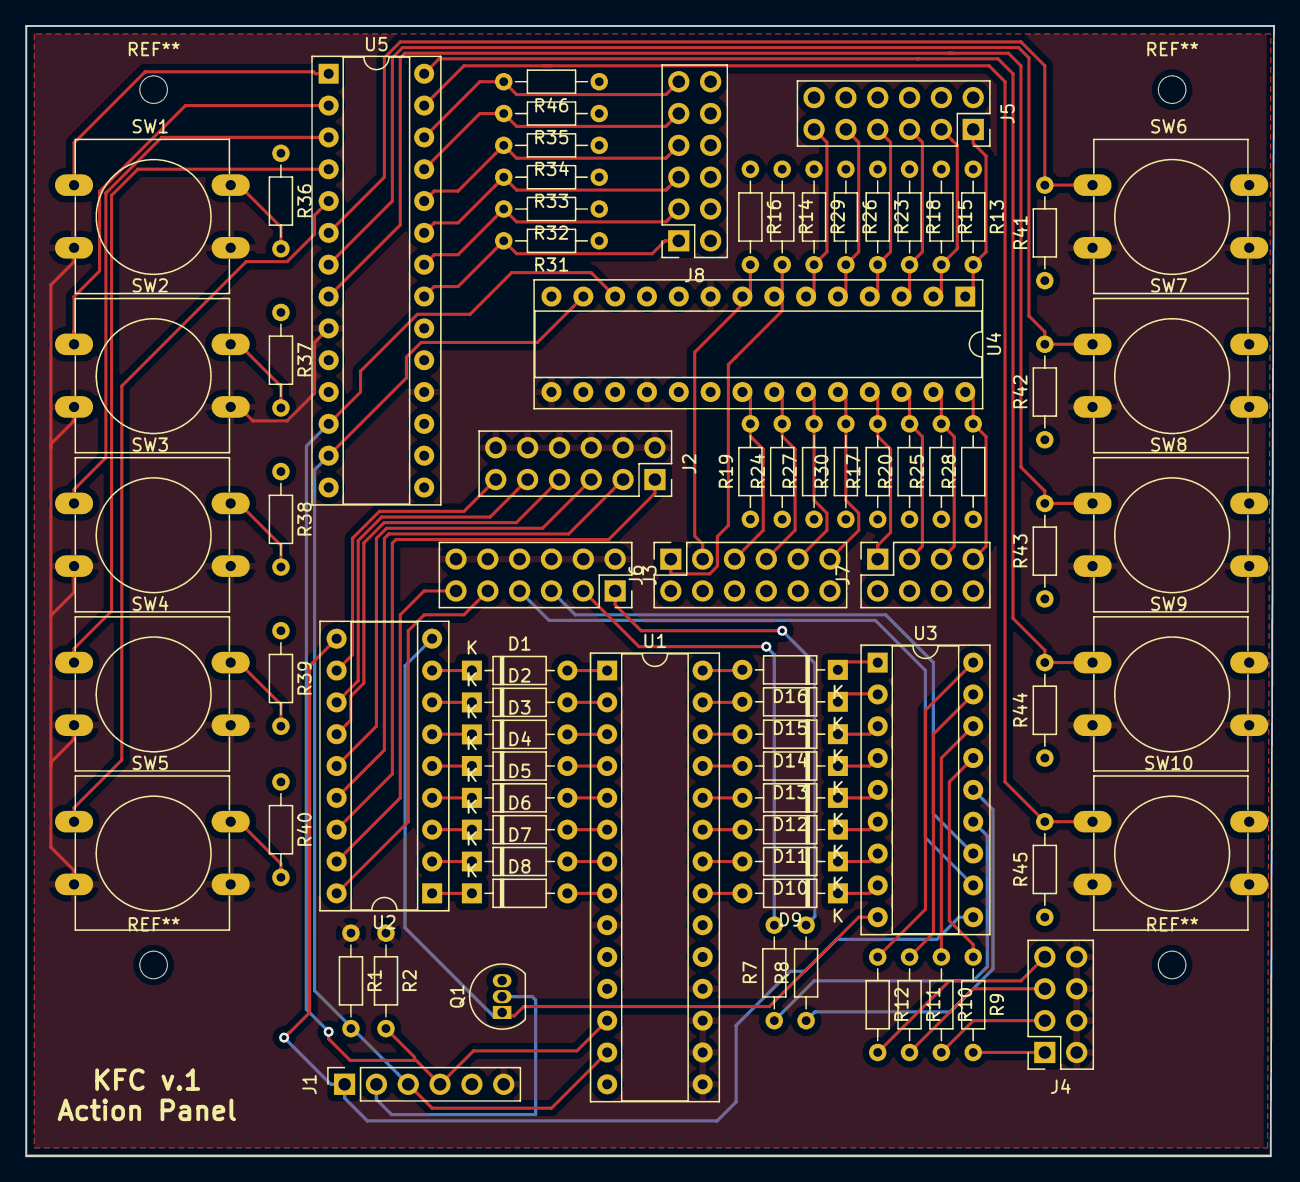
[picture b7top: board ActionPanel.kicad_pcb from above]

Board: 2 copper layers, 99.6 x 90.2 mm, 80 parts (0 on the bottom side), 93 nets.

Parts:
D1, D2, D3, D4, D5, D6, D7, D8, D9, D10, D11, D12, D13, D14, D15, D16: D; D_DO-35_SOD27_P7.62mm_Horizontal
J1: Conn_01x06; PinSocket_1x06_P2.54mm_Vertical
J2, J3, J5, J6, J8: Conn_02x06_Odd_Even; PinSocket_2x06_P2.54mm_Vertical
J4, J7: Conn_02x04_Odd_Even; PinSocket_2x04_P2.54mm_Vertical
Q1: 2N3906; TO-92_Inline
R1, R2, R13, R14, R15, R16, R17, R18, R19, R20, R23, R24, R25, R26, R27, R28, R29, R30, R32, R33, R34, R35, R36, R37, R38, R39, R40, R41, R42, R43, R44, R45, R46: R; R_Axial_DIN0204_L3.6mm_D1.6mm_P7.62mm_Horizontal
R7, R8, R9, R10, R11, R12: 100; R_Axial_DIN0204_L3.6mm_D1.6mm_P7.62mm_Horizontal
R31: 4.7k; R_Axial_DIN0204_L3.6mm_D1.6mm_P7.62mm_Horizontal
SW1, SW2, SW3, SW4, SW5, SW6, SW7, SW8, SW9, SW10: SW_SPST; SW_PUSH-12mm
U1, U4, U5: MCP23017_SP; DIP-28_W7.62mm_Socket
U2, U3: ULN2803A; DIP-18_W7.62mm_Socket

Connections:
+5V: J1.6, J2.2, J2.4, J2.6, J2.8, J2.10, J2.12, J3.2, J3.4, J3.6, J3.8, J3.10, J3.12, J4.2, J4.4, J4.6, J4.8, R1.1, R2.1, SW1.2, SW2.2, SW3.2, SW4.2, SW5.2, SW6.2, SW7.2, SW8.2, SW9.2, SW10.2, U1.9, U1.15, U1.16, U1.17, U1.18, U4.9, U4.15, U4.18, U5.9, U5.18
/AG1: R36.2, SW1.1, U5.1
/AG2: R37.2, SW2.1, U5.2
/AG3: R38.2, SW3.1, U5.3
/AG4: R39.2, SW4.1, U5.4
/AG5: R40.2, SW5.1, U5.5
/AG6: R41.2, SW6.1, U5.6
/AG7: R42.2, SW7.1, U5.7
/AG8: R43.2, SW8.1, U5.8
/AG9: R44.2, SW9.1, U5.28
/AG10: R45.2, SW10.1, U5.27
/ASW: J8.11, R46.2, U5.26
/ATB: J6.11, R30.2, U4.24
/BRKL: R9.1, U3.15
/BSW: J8.5, R33.2, U5.23
/DIM: Q1.1, U2.9, U3.9
/GRL: R8.1, U3.14
/GSW: J8.3, R32.2, U5.22
/LGTL: R7.1, U3.13
/LSW: J8.1, R31.2, U5.21
/LTEST: J1.1, U2.10, U3.10
/RCSL: R10.1, U3.16
/RST: J7.1, R17.2, U4.25
/RSW: J8.7, R34.2, U5.24
/SAS1: J5.1, R13.2, U4.1
/SAS2: J5.3, R15.2, U4.2
/SAS3: J5.5, R18.2, U4.3
/SAS4: J5.7, R23.2, U4.4
/SAS5: J5.9, R26.2, U4.5
/SAS6: J5.11, R29.2, U4.6
/SAS7: J6.1, R14.2, U4.7
/SAS8: J6.3, R16.2, U4.8
/SAS9: J6.5, R19.2, U4.21
/SAS10: J6.7, R24.2, U4.22
/SASC: J6.9, R27.2, U4.23
/SASL1: J2.11, U2.11
/SASL2: J2.9, U2.12
/SASL3: J2.7, U2.13
/SASL4: J2.5, U2.14
/SASL5: J2.3, U2.15
/SASL6: J2.1, U2.16
/SASL7: J3.11, U2.17
/SASL8: J3.9, U2.18
/SASL9: J3.7, U3.11
/SASL10: J3.5, U3.12
/SCK: J1.4, R2.2, U1.12, U4.12, U5.12
/SDA: J1.3, R1.2, U1.13, U4.13, U5.13
/STSW: J8.9, R35.2, U5.25
/UNI1: R11.1, U3.17
/UNI2: R12.1, U3.18
/UNO1: J7.3, R20.2, U4.26
/UNO2: J7.5, R25.2, U4.27
/UNO3: J7.7, R28.2, U4.28
GND: J1.5, J5.2, J5.4, J5.6, J5.8, J5.10, J5.12, J6.2, J6.4, J6.6, J6.8, J6.10, J6.12, J7.2, J7.4, J7.6, J7.8, J8.2, J8.4, J8.6, J8.8, J8.10, J8.12, Q1.3, R13.1, R14.1, R15.1, R16.1, R17.1, R18.1, R19.1, R20.1, R23.1, R24.1, R25.1, R26.1, R27.1, R28.1, R29.1, R30.1, R31.1, R32.1, R33.1, R34.1, R35.1, R36.1, R37.1, R38.1, R39.1, R40.1, R41.1, R42.1, R43.1, R44.1, R45.1, R46.1, U1.10, U4.10, U4.16, U4.17, U5.10, U5.15, U5.16, U5.17
unnamed: D1.1, U2.8
unnamed: D1.2, U1.1
unnamed: D2.1, U2.7
unnamed: D2.2, U1.2
unnamed: D3.1, U2.6
unnamed: D3.2, U1.3
unnamed: D4.1, U2.5
unnamed: D4.2, U1.4
unnamed: D5.1, U2.4
unnamed: D5.2, U1.5
unnamed: D6.1, U2.3
unnamed: D6.2, U1.6
unnamed: D7.1, U2.2
unnamed: D7.2, U1.7
unnamed: D8.1, U2.1
unnamed: D8.2, U1.8
unnamed: D9.1, U3.8
unnamed: D9.2, U1.21
unnamed: D10.1, U3.7
unnamed: D10.2, U1.22
unnamed: D11.1, U3.6
unnamed: D11.2, U1.23
unnamed: D12.1, U3.5
unnamed: D12.2, U1.24
unnamed: D13.1, U3.4
unnamed: D13.2, U1.25
unnamed: D14.1, U3.3
unnamed: D14.2, U1.26
unnamed: D15.1, U3.2
unnamed: D15.2, U1.27
unnamed: D16.1, U3.1
unnamed: D16.2, U1.28
unnamed: J1.2, Q1.2
unnamed: J3.1, R8.2
unnamed: J3.3, R7.2
unnamed: J4.1, R9.2
unnamed: J4.3, R10.2
unnamed: J4.5, R11.2
unnamed: J4.7, R12.2
